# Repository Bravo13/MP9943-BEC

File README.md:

# Matek micro BEC 6-30V to 5V/9V reverse

## What
This is pretty simple and small DC-DC stepdown converter with input 6-30v and 1.5A current. Output can be adjusted to 5v(default) and 9v(JP1 soldered) Based on [MP9943](https://www.mouser.com/pdfDocs/MP9943_r11-1384533.pdf) chip.

## Why?
Just for fun, checking how hard it will be to reverse-design pcbs

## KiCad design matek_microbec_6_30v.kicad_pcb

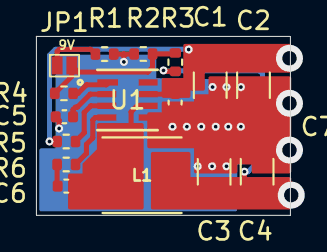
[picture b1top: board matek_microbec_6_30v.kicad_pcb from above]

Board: 2 copper layers, 14.1 x 9.9 mm, 16 parts (0 on the bottom side), 11 nets.

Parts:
C1, C2: 14uF; C_1206_3216Metric
C3, C4: 27uF; C_1206_3216Metric
C5, C6, C7: 0.1uF; C_0402_1005Metric
JP1: 9V; SolderJumper-2_P1.3mm_Open_Pad0.6x1mm
L1: L; IND_ASPI-4020HI-R10M-T
R1: 200k; R_0402_1005Metric
R2: 6.8k; R_0402_1005Metric
R3: 35.6k; R_0402_1005Metric
R4: 51.2k; R_0402_1005Metric
R5: 1M; R_0402_1005Metric
R6: 22R; R_0402_1005Metric
U1: MP9943GQ-Z; QFN-8_MP9943_MNP

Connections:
/+IN: C1.1, C2.1, C7.1, R5.1, U1.7 (IN)
/+OUT: C3.1, C4.1, L1.2, R3.2
GND: C1.2, C2.2, C3.2, C4.2, C5.2, C7.2, R1.1, R2.1, U1.5 (GND)
unnamed: C6.2, R6.2
unnamed: JP1.1 (A), R1.2
unnamed: JP1.2 (B), R2.2, R3.1, R4.1
unnamed: R6.1, U1.4 (BST)
unnamed: R5.2, U1.3 (EN/SYNC)
unnamed: R4.2, U1.1 (FB)
unnamed: C6.1, L1.1, U1.6 (SW)
unnamed: C5.1, U1.2 (VCC)

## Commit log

2024-08-02 init
2024-08-02 step file
